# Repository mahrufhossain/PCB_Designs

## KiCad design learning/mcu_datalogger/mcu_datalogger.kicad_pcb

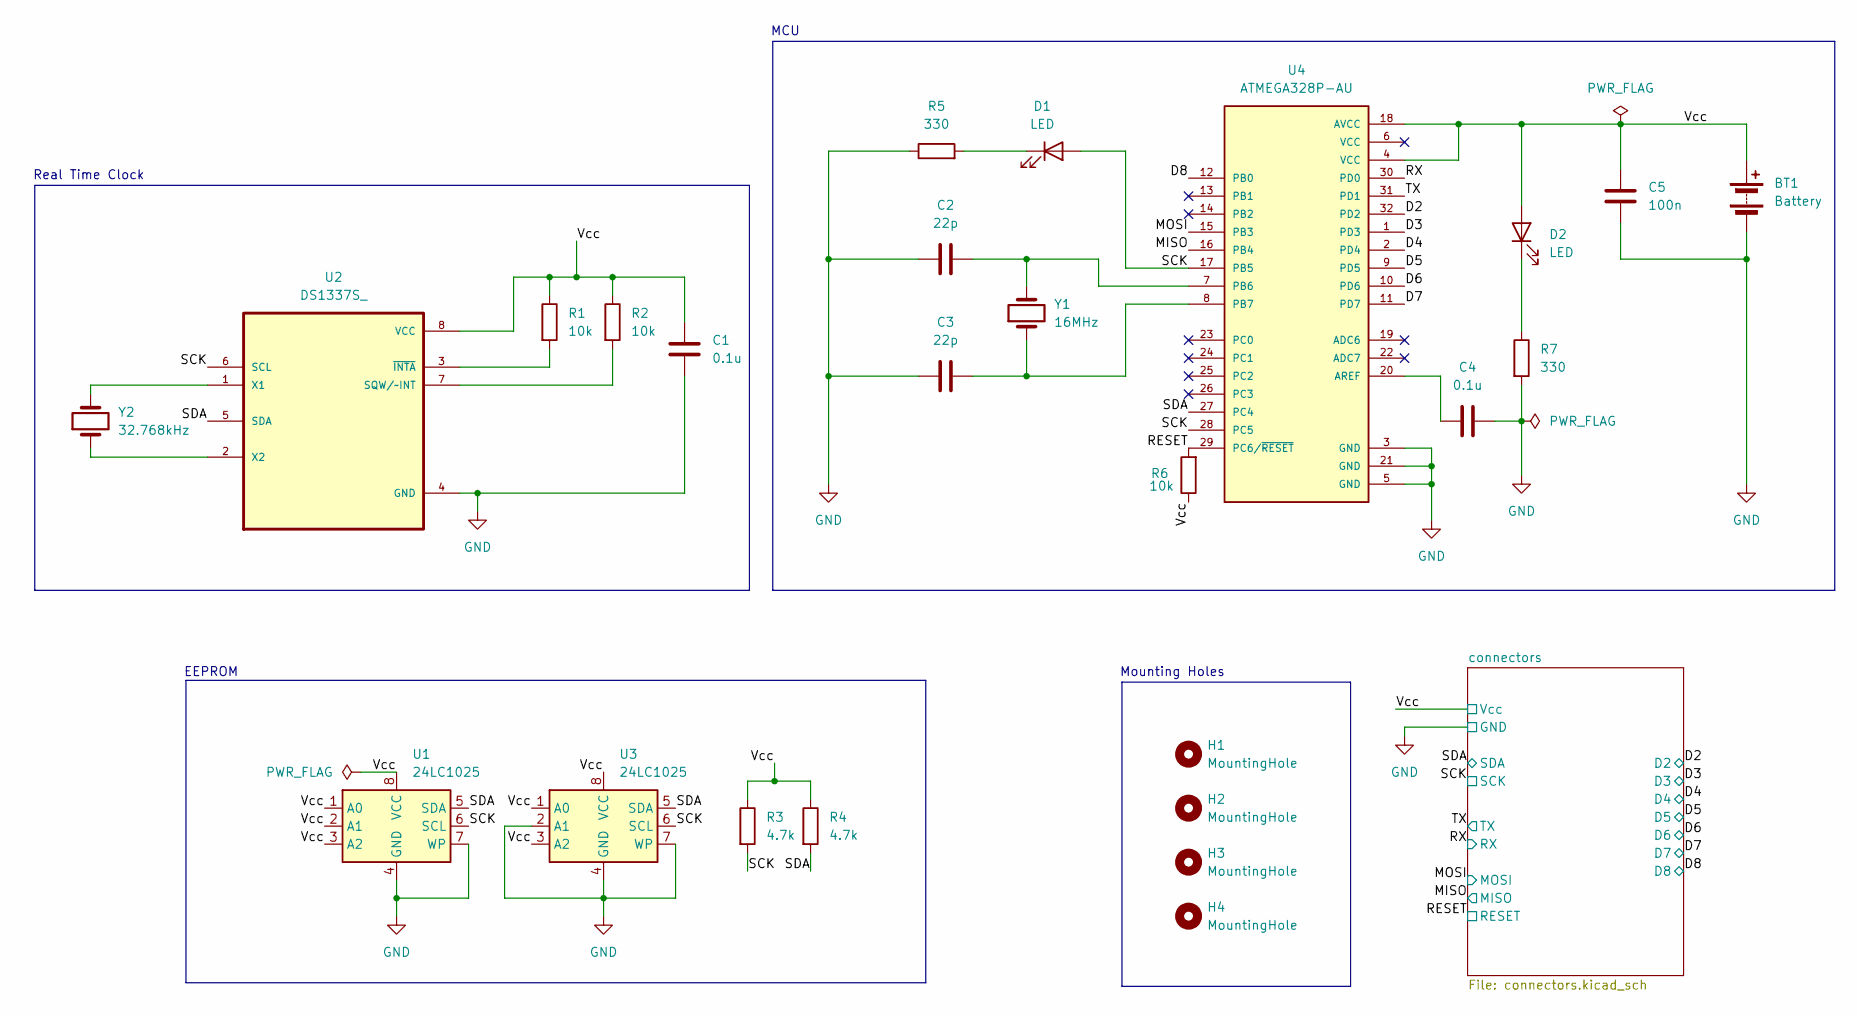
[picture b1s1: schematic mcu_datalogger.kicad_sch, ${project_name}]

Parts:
BT1: Battery; PinHeader_1x02_P2.54mm_Vertical
C1, C4: 0.1u; C_0805_2012Metric
C2, C3: 22p; C_0805_2012Metric
C5: 100n; C_0805_2012Metric
D1, D2: LED; LED_0805_2012Metric
H1, H2, H3, H4: MountingHole; MountingHole_2.1mm
R1, R2, R6: 10k; R_0805_2012Metric
R3, R4: 4.7k; R_0805_2012Metric
R5, R7: 330; R_0805_2012Metric
U1, U3: 24LC1025; SOIC-8_5.3x5.3mm_P1.27mm
U2: DS1337S_; SOIC127P600X175-8N
U4: ATMEGA328P-AU; QFP80P900X900X120-32N; PARTREV 8271A
Y1: 16MHz; Crystal_SMD_5032-2Pin_5.0x3.2mm_HandSoldering
Y2: 32.768kHz; Crystal_SMD_5032-2Pin_5.0x3.2mm_HandSoldering

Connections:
/D2: U4.32 (PD2); also elsewhere on the board
/D3: U4.1 (PD3); also elsewhere on the board
/D4: U4.2 (PD4); also elsewhere on the board
/D5: U4.9 (PD5); also elsewhere on the board
/D6: U4.10 (PD6); also elsewhere on the board
/D7: U4.11 (PD7); also elsewhere on the board
/D8: U4.12 (PB0); also elsewhere on the board
/MISO: U4.16 (PB4); also elsewhere on the board
/MOSI: U4.15 (PB3); also elsewhere on the board
/RESET: R6.2, U4.29 (PC6/~RESET); also elsewhere on the board
/RX: U4.30 (PD0); also elsewhere on the board
/SCK: D1.2 (A), R3.2, U1.6 (SCL), U2.6 (SCL), U3.6 (SCL), U4.17 (PB5), U4.28 (PC5); also elsewhere on the board
/SDA: R4.2, U1.5 (SDA), U2.5 (SDA), U3.5 (SDA), U4.27 (PC4); also elsewhere on the board
/TX: U4.31 (PD1); also elsewhere on the board
/Vcc: BT1.1 (+), C1.1, C5.1, D2.2 (A), R1.1, R2.1, R3.1, R4.1, R6.1, U1.1 (A0), U1.2 (A1), U1.3 (A2), U1.8 (VCC), U2.8 (VCC), U3.1 (A0), U3.3 (A2), U3.8 (VCC), U4.4 (VCC), U4.18 (AVCC); also elsewhere on the board
GND: BT1.2 (-), C1.2, C2.1, C3.1, C4.2, C5.2, R5.1, R7.2, U1.4 (GND), U1.7 (WP), U2.4 (GND), U3.2 (A1), U3.4 (GND), U3.7 (WP), U4.3 (GND), U4.5 (GND), U4.21 (GND); also elsewhere on the board
unnamed: D1.1 (K), R5.2
unnamed: D2.1 (K), R7.1
unnamed: R2.2, U2.7 (SQW/~INT)
unnamed: U2.1 (X1), Y2.2
unnamed: U2.2 (X2), Y2.1
unnamed: R1.2, U2.3 (~INTA)
unnamed: C4.1, U4.20 (AREF)
unnamed: C2.2, U4.7 (PB6), Y1.2
unnamed: C3.2, U4.8 (PB7), Y1.1

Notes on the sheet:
EEPROM
MCU
Mounting Holes
Real Time Clock

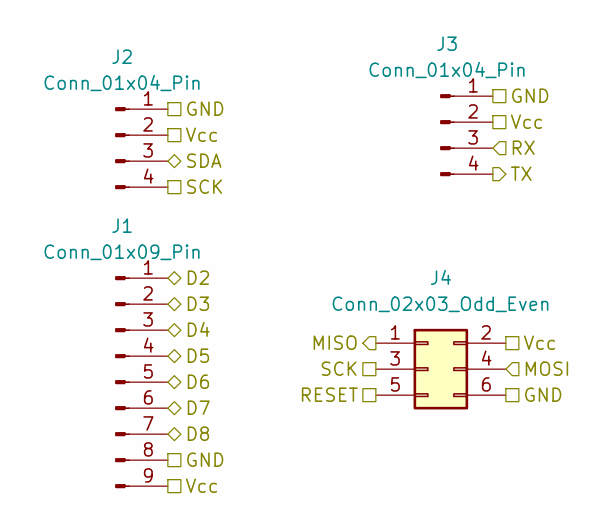
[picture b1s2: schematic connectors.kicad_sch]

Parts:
J1: Conn_01x09_Pin; PinHeader_1x09_P2.54mm_Vertical
J2, J3: Conn_01x04_Pin; PinHeader_1x04_P2.54mm_Vertical
J4: Conn_02x03_Odd_Even; PinHeader_2x03_P2.54mm_Vertical

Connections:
/D2: J1.1; also elsewhere on the board
/D3: J1.2; also elsewhere on the board
/D4: J1.3; also elsewhere on the board
/D5: J1.4; also elsewhere on the board
/D6: J1.5; also elsewhere on the board
/D7: J1.6; also elsewhere on the board
/D8: J1.7; also elsewhere on the board
/MISO: J4.1; also elsewhere on the board
/MOSI: J4.4; also elsewhere on the board
/RESET: J4.5; also elsewhere on the board
/RX: J3.3; also elsewhere on the board
/SCK: J2.4, J4.3; also elsewhere on the board
/SDA: J2.3; also elsewhere on the board
/TX: J3.4; also elsewhere on the board
/Vcc: J1.9, J2.2, J3.2, J4.2; also elsewhere on the board
GND: J1.8, J2.1, J3.1, J4.6; also elsewhere on the board

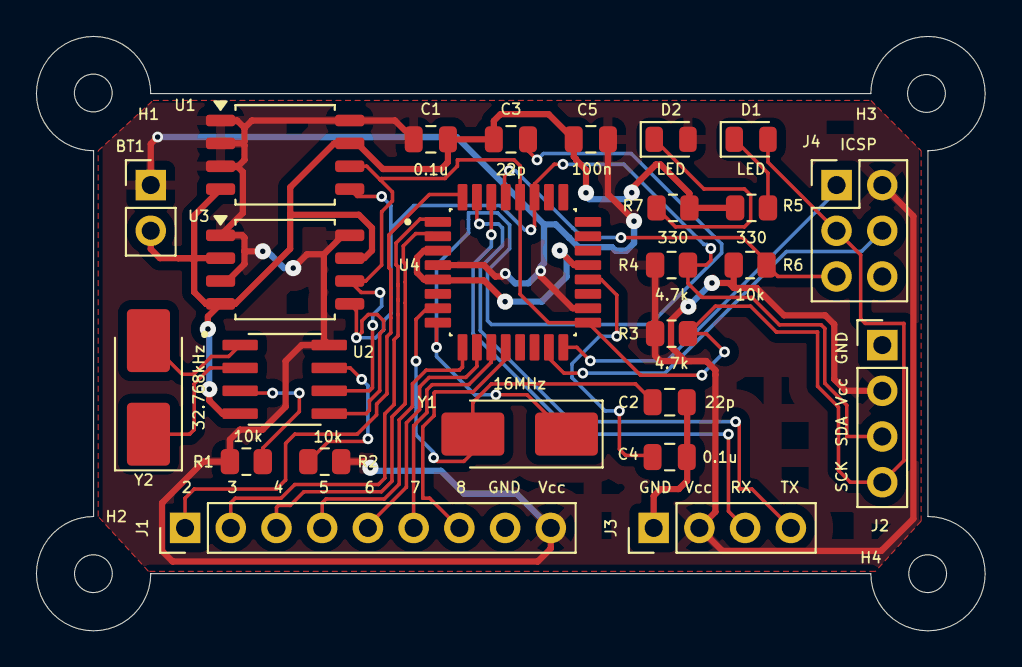
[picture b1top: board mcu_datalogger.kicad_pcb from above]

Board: 2 copper layers, 52.7 x 33.0 mm, 29 parts (0 on the bottom side), 25 nets.

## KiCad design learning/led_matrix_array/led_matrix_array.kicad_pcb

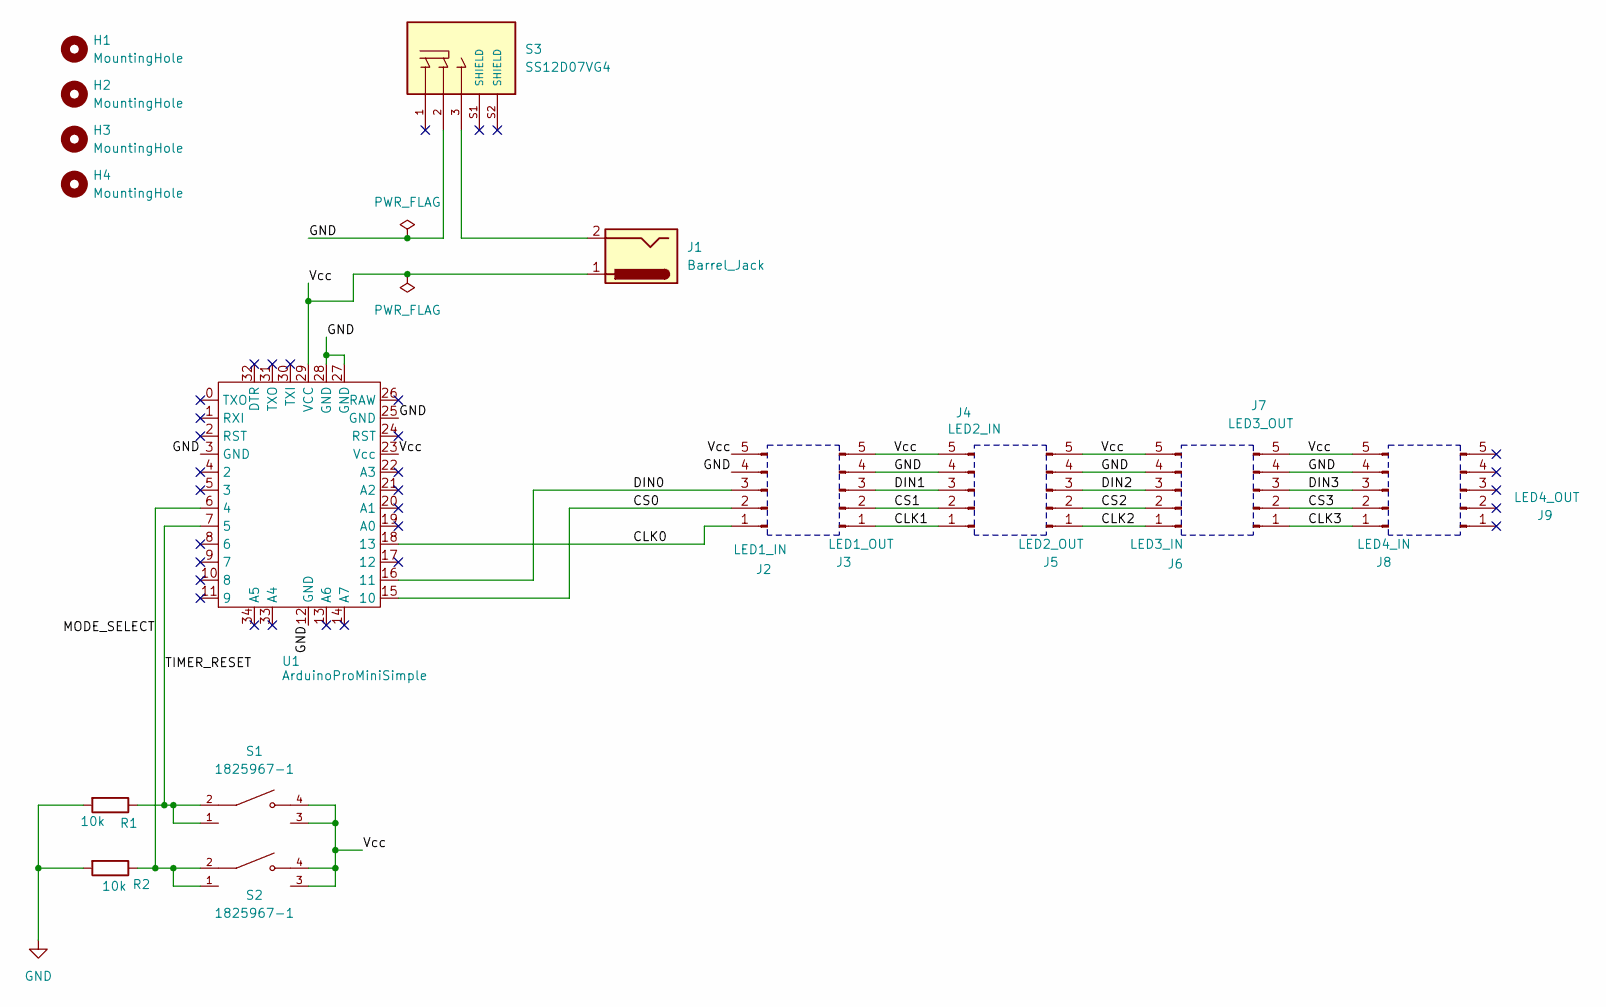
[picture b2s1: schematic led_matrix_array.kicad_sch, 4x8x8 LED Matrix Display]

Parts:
H1, H2, H3, H4: MountingHole; MountingHole_2.5mm
J1: Barrel_Jack; BarrelJack_Horizontal
J2: LED1_IN; PinHeader_1x05_P2.54mm_Vertical
J3: LED1_OUT; PinHeader_1x05_P2.54mm_Vertical
J4: LED2_IN; PinHeader_1x05_P2.54mm_Vertical
J5: LED2_OUT; PinHeader_1x05_P2.54mm_Vertical
J6: LED3_IN; PinHeader_1x05_P2.54mm_Vertical
J7: LED3_OUT; PinHeader_1x05_P2.54mm_Vertical
J8: LED4_IN; PinHeader_1x05_P2.54mm_Vertical
J9: LED4_OUT; PinHeader_1x05_P2.54mm_Vertical
R1, R2: 10k; R_Axial_DIN0204_L3.6mm_D1.6mm_P7.62mm_Horizontal
S1, S2: 1825967-1; SW_1825967-1
S3: SS12D07VG4; SW_SS12D07VG4; PARTREV 1
U1: ArduinoProMiniSimple; ArduinoProMiniCustom

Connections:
/CLK0: J2.1, U1.18 (13)
/CLK1: J3.1, J4.1
/CLK2: J5.1, J6.1
/CLK3: J7.1, J8.1
/CS0: J2.2, U1.15 (10)
/CS1: J3.2, J4.2
/CS2: J5.2, J6.2
/CS3: J7.2, J8.2
/DIN0: J2.3, U1.16 (11)
/DIN1: J3.3, J4.3
/DIN2: J5.3, J6.3
/DIN3: J7.3, J8.3
/MODE_SELECT: R2.1, S2.1, S2.2, U1.6 (4)
/TIMER_RESET: R1.1, S1.1, S1.2, U1.7 (5)
/Vcc: J1.1, J2.5, J3.5, J4.5, J5.5, J6.5, J7.5, J8.5, S1.3, S1.4, S2.3, S2.4, U1.23 (Vcc), U1.29 (VCC)
GND: J2.4, J3.4, J4.4, J5.4, J6.4, J7.4, J8.4, R1.2, R2.2, S3.2, U1.3 (GND), U1.12 (GND), U1.25 (GND), U1.27 (GND), U1.28 (GND)
unnamed: J1.2, S3.3

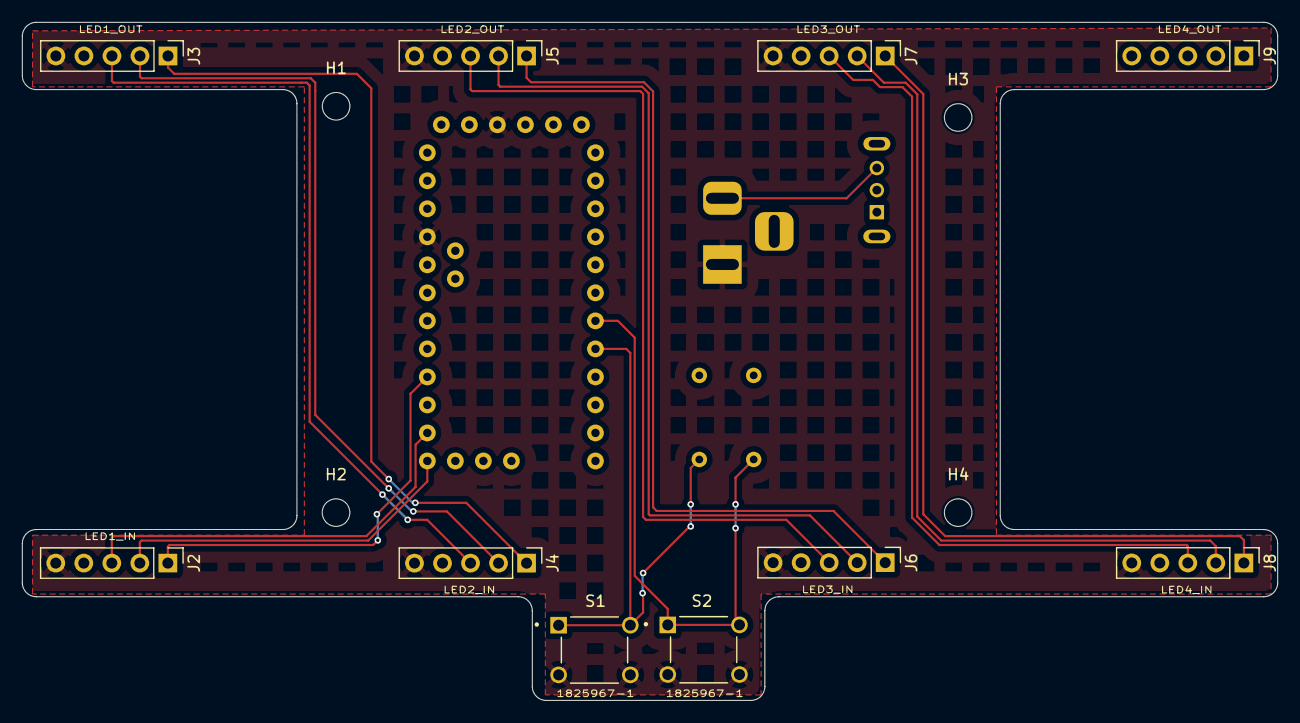
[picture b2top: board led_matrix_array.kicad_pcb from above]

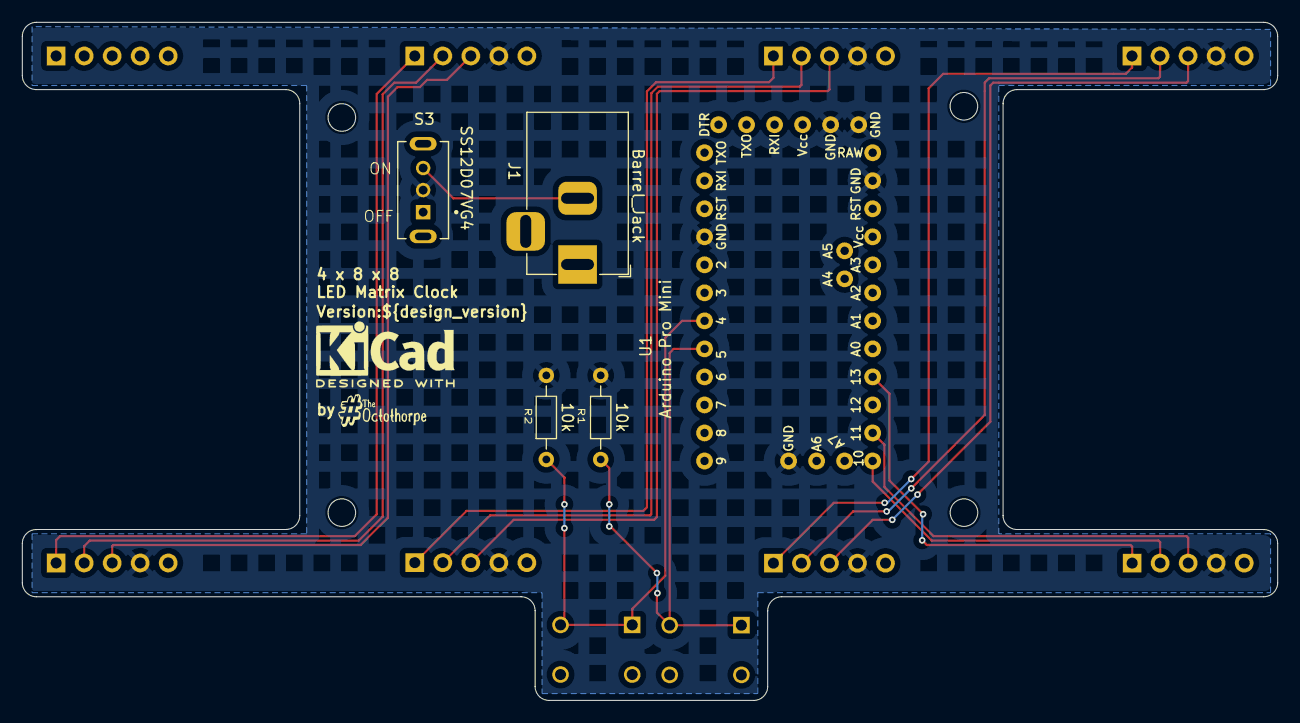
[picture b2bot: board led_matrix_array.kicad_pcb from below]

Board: 2 copper layers, 113.8 x 61.5 mm, 19 parts (5 on the bottom side), 17 nets.

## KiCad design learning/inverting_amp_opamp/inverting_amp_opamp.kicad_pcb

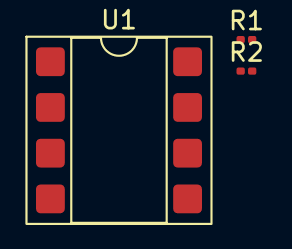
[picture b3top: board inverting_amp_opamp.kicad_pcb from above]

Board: 2 copper layers, 3 parts (0 on the bottom side), 2 nets, no tracks yet.

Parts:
R1: 1k; R_0201_0603Metric
R2: 100k; R_0201_0603Metric
U1: LM741; DIP-8_W7.62mm_SMDSocket_SmallPads

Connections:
unnamed: R2.2, U1.6
unnamed: R1.1, R2.1, U1.3 (+)

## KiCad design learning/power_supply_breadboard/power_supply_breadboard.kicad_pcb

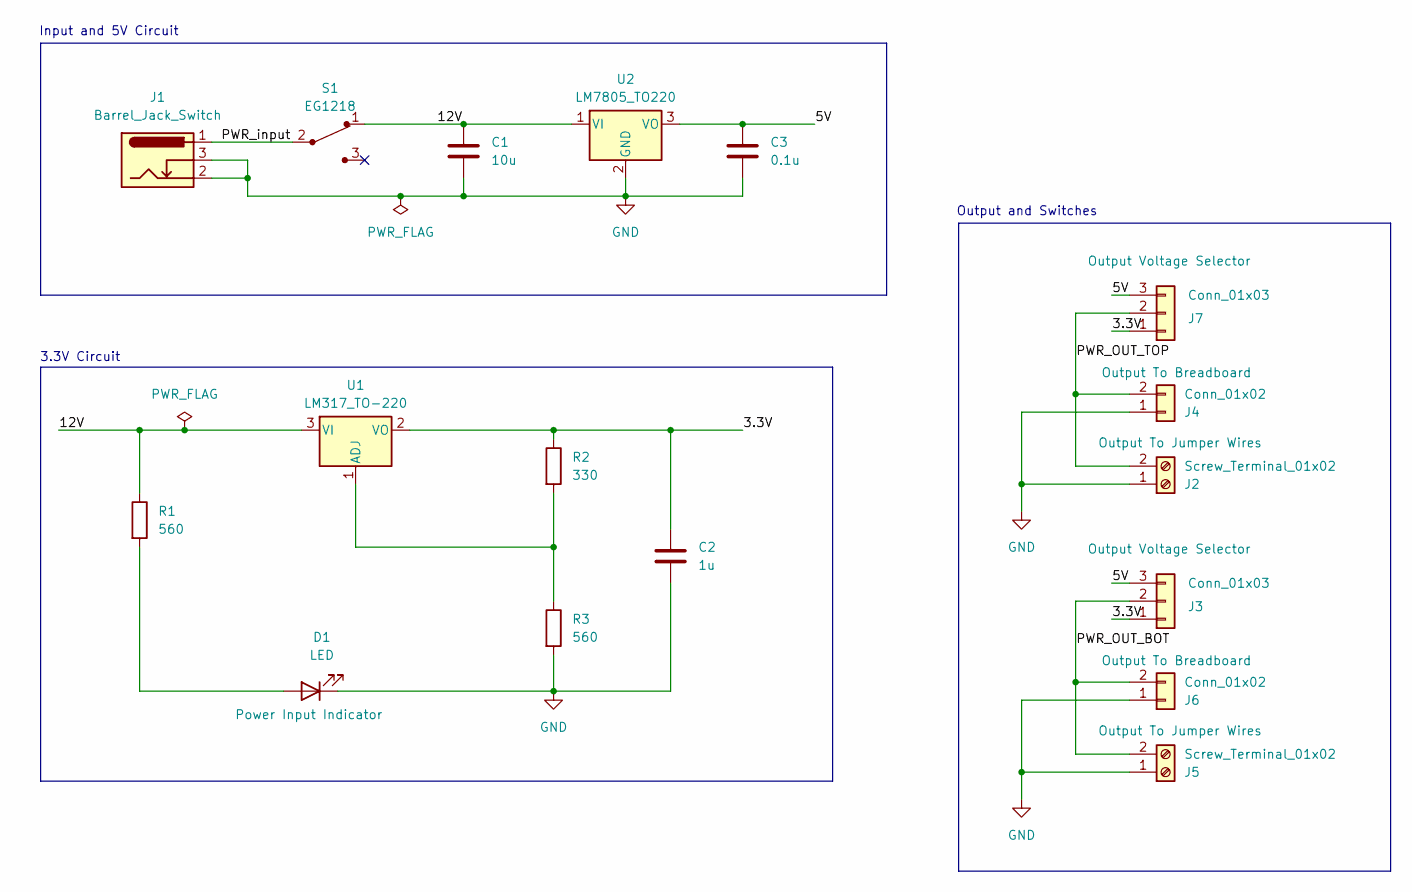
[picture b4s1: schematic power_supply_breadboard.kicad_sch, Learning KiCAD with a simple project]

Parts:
C1: 10u; C_Disc_D3.0mm_W1.6mm_P2.50mm
C2: 1u; C_Disc_D3.0mm_W1.6mm_P2.50mm
C3: 0.1u; C_Disc_D3.0mm_W1.6mm_P2.50mm
D1: LED; LED_D5.0mm
J1: Barrel_Jack_Switch; BarrelJack_Horizontal
J2, J5: Screw_Terminal_01x02; TerminalBlock_MaiXu_MX126-5.0-02P_1x02_P5.00mm
J3, J7: Conn_01x03; PinHeader_1x03_P2.54mm_Vertical
J4, J6: Conn_01x02; PinHeader_1x02_P2.54mm_Vertical
R1, R3: 560; R_Axial_DIN0204_L3.6mm_D1.6mm_P7.62mm_Horizontal
R2: 330; R_Axial_DIN0204_L3.6mm_D1.6mm_P7.62mm_Horizontal
S1: EG1218; Switch_Slide_11.6x4mm_EG1218; MPN EG1218; Digi-Key_PN EG1903-ND
U1: LM317_TO-220; TO-220-3_Vertical
U2: LM7805_TO220; TO-220-3_Vertical

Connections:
/3.3V: C2.1, J3.1, J7.1, R2.1, U1.2 (VO)
/5V: C3.1, J3.3, J7.3, U2.3 (VO)
/12V: C1.1, R1.1, S1.1, U1.3 (VI), U2.1 (VI)
/PWR_OUT_BOT: J3.2, J5.2, J6.2
/PWR_OUT_TOP: J2.2, J4.2, J7.2
/PWR_input: J1.1, S1.2
GND: C1.2, C2.2, C3.2, D1.1 (K), J1.2, J1.3, J2.1, J4.1, J5.1, J6.1, R3.2, U2.2 (GND)
unnamed: D1.2 (A), R1.2
unnamed: R2.2, R3.1, U1.1 (ADJ)

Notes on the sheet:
3.3V Circuit
Output and Switches
Input and 5V Circuit

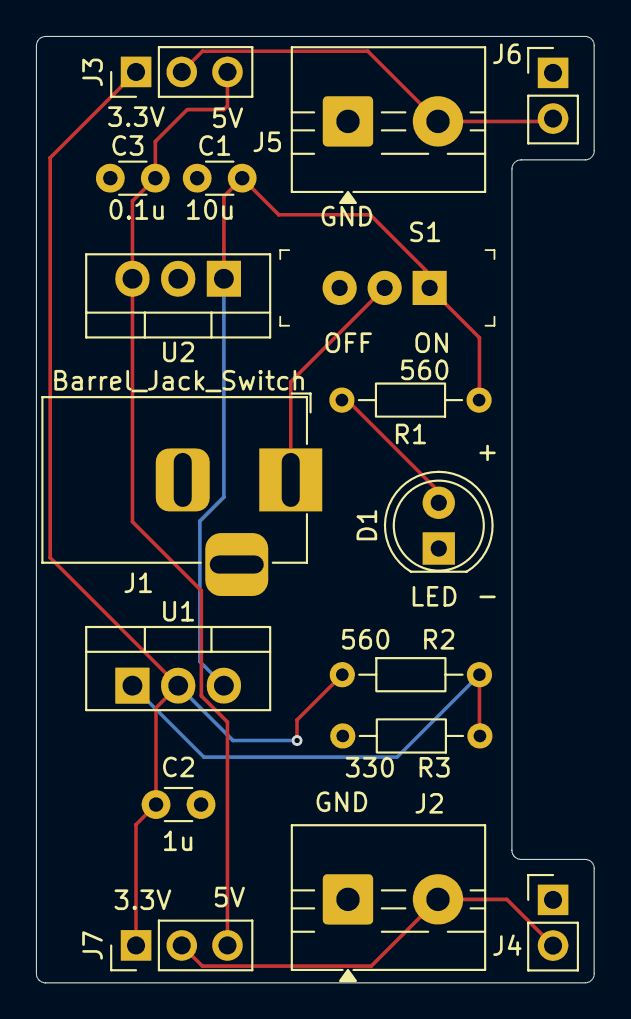
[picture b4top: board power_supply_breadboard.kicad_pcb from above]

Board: 2 copper layers, 31.0 x 52.6 mm, 17 parts (0 on the bottom side), 9 nets.

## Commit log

2025-11-02 Did some learning projects on breadboard power supply and 4x8x8 LED matrix display
2025-11-02 Added gitignore file
2025-11-02 Setup of schematic editor for a new project
2025-11-02 Changed the logo location
2025-11-02 Have added required symbols to the schematic sheets.
2025-11-02 Finished the schematic design
2025-11-02 Finished mcu datalogger schematic design
2025-11-02 Setup pcb editor
2025-11-02 Added all the footprints to the pcb editor
2025-11-02 Redefined shape and layout
2025-11-02 Finished layout of the pcb
2025-11-02 Finished the project
2025-11-03 Fixed track width issues
2025-11-03 Completed last check and generated gerber files
2025-11-03 Added gerber directories to gitignore
